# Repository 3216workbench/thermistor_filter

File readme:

project made for pcbway assembly

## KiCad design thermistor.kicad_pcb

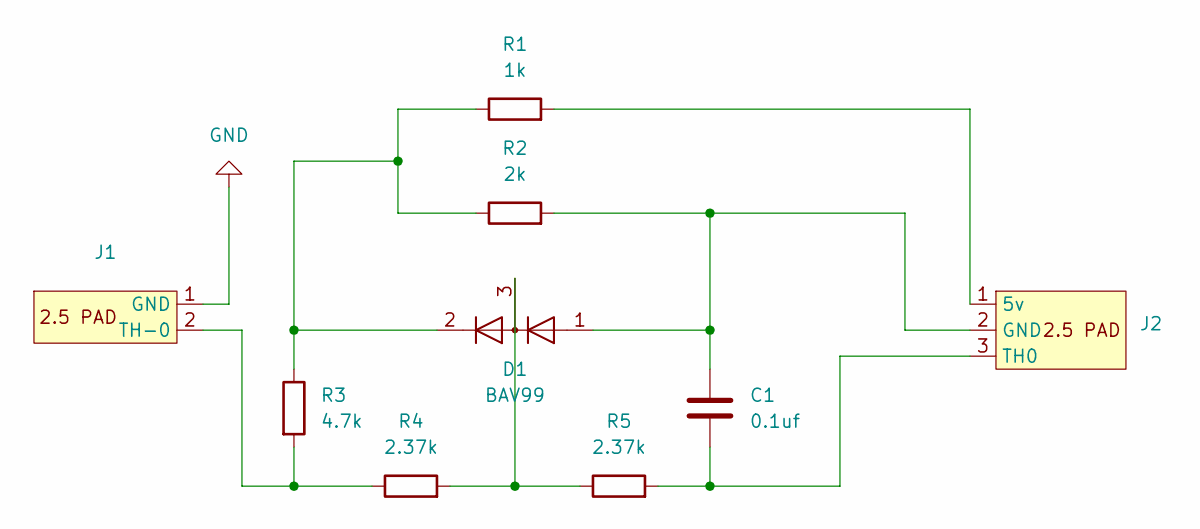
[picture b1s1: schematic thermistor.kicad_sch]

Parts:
C1: 0.1uf; C_0402_1005Metric
D1: BAV99; SOT-23
J1: 2_pin_2.5pitch_solder_pads
J2: 3_pin_2.5pitch_solder_pads
R1: 1k; R_0402_1005Metric
R2: 2k; R_0402_1005Metric
R3: 4.7k; R_0402_1005Metric
R4, R5: 2.37k; R_0402_1005Metric

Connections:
GND: J1.1 (GND)
unnamed: D1.2 (A), R1.1, R2.1, R3.1
unnamed: D1.3 (K), R4.2, R5.1
unnamed: J1.2 (TH-0), R3.2, R4.1
unnamed: J2.1 (5v), R1.2
unnamed: C1.1, D1.1 (K), J2.2 (GND), R2.2
unnamed: C1.2, J2.3 (TH0), R5.2

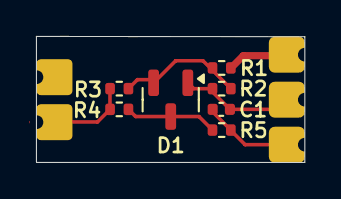
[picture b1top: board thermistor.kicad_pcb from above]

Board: 2 copper layers, 14.9 x 7.0 mm, 9 parts (0 on the bottom side), 6 nets.
